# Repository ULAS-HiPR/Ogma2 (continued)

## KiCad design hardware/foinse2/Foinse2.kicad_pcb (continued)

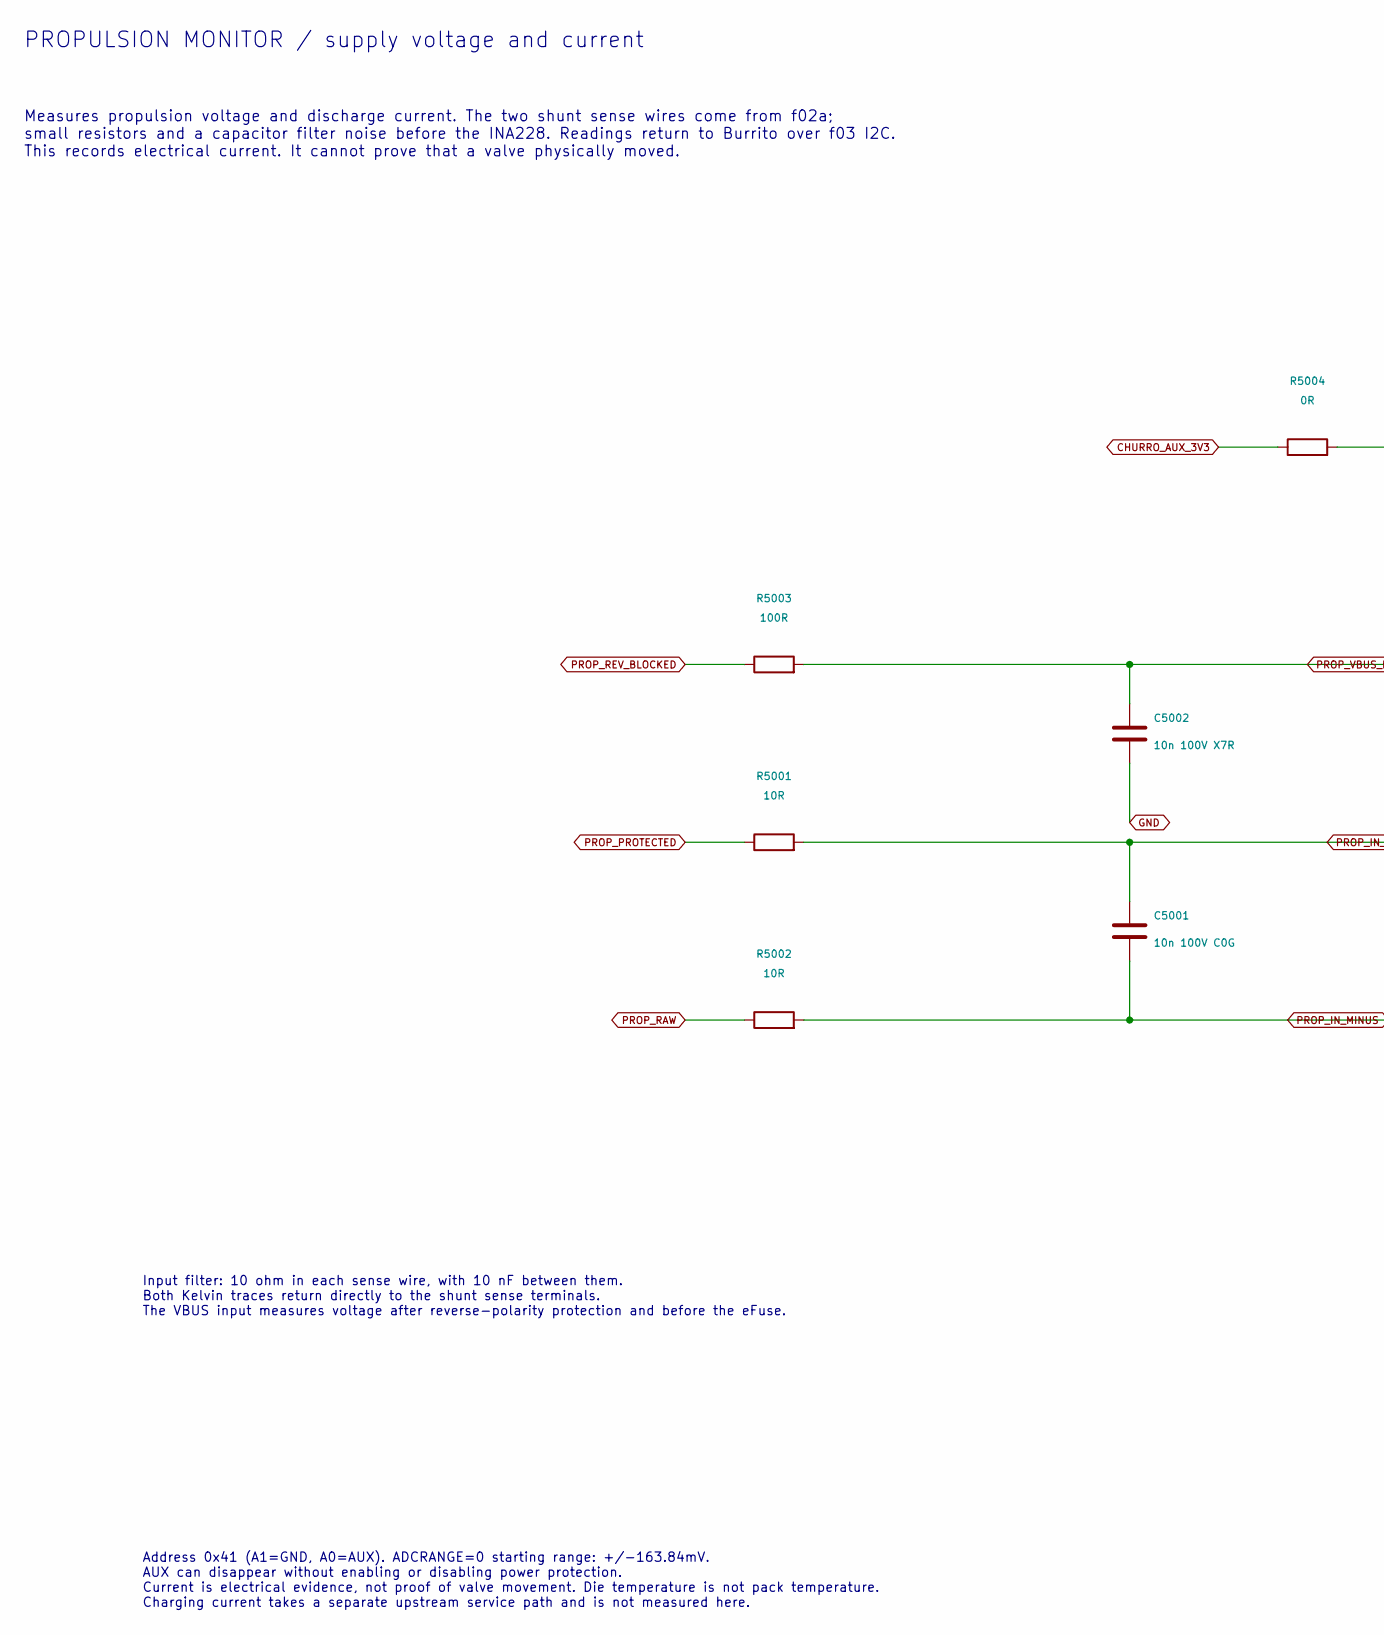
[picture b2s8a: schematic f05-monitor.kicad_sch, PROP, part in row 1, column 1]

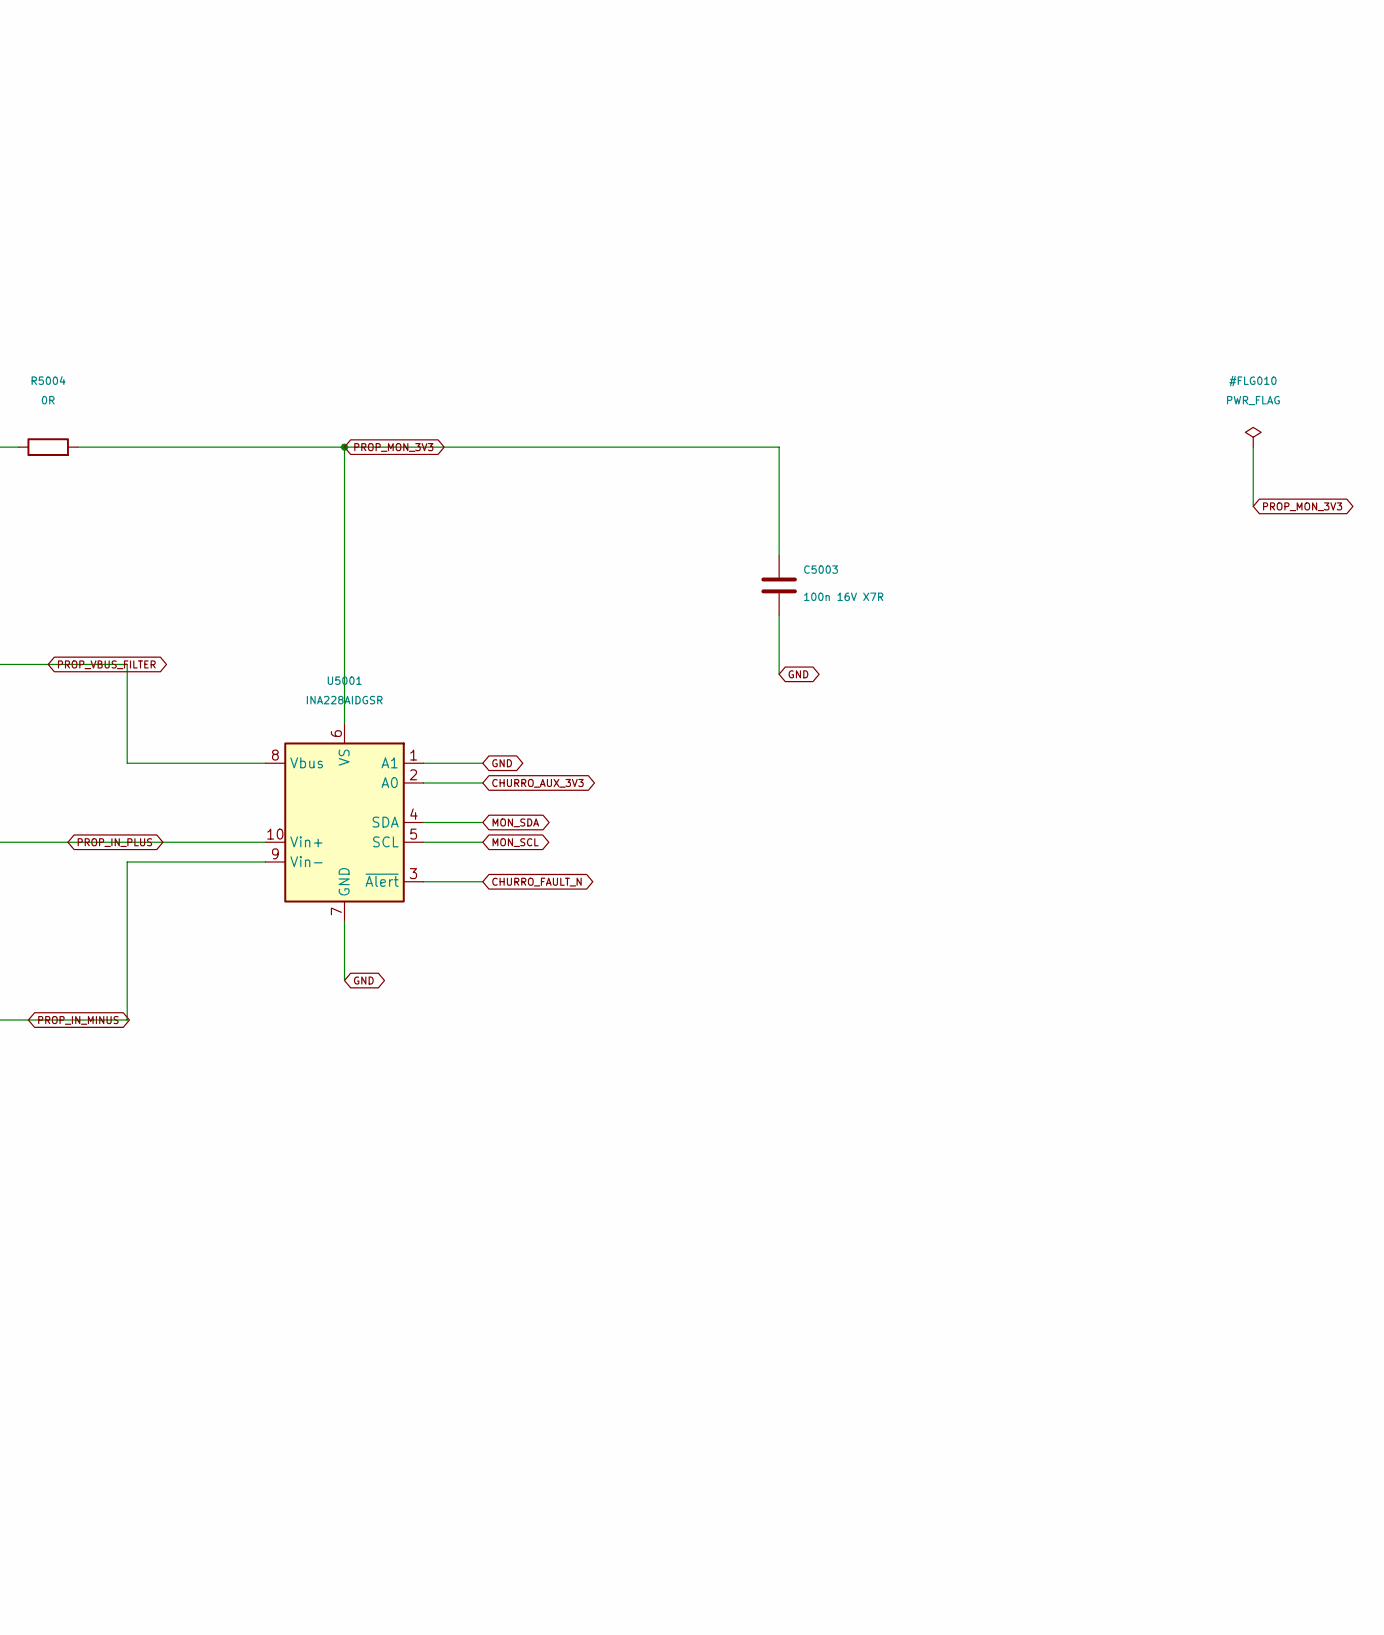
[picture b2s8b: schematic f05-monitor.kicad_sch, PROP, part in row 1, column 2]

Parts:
C5001: 10n 100V C0G; C_0603_1608Metric
C5002: 10n 100V X7R; C_0603_1608Metric
C5003: 100n 16V X7R; C_0603_1608Metric
R5001, R5002: 10R; R_0603_1608Metric
R5003: 100R; R_0603_1608Metric
R5004: 0R; R_0603_1608Metric
U5001: INA228AIDGSR; MPN INA228AIDGSR

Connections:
CHURRO_AUX_3V3: R5004.1, U5001.2 (A0); also elsewhere on the board
CHURRO_FAULT_N: U5001.3 (~Alert); also elsewhere on the board
GND: C5002.2, C5003.2, U5001.1 (A1), U5001.7 (GND); also elsewhere on the board
MON_SCL: U5001.5 (SCL); also elsewhere on the board
MON_SDA: U5001.4 (SDA); also elsewhere on the board
PROP_IN_MINUS: C5001.2, R5002.2, U5001.9 (Vin-)
PROP_IN_PLUS: C5001.1, R5001.2, U5001.10 (Vin+)
PROP_MON_3V3: C5003.1, R5004.2, U5001.6 (VS)
PROP_PROTECTED: R5001.1; also elsewhere on the board
PROP_RAW: R5002.1; also elsewhere on the board
PROP_REV_BLOCKED: R5003.1; also elsewhere on the board
PROP_VBUS_FILTER: C5002.1, R5003.2, U5001.8 (Vbus)

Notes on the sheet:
PROPULSION MONITOR / supply voltage and current
Input filter: 10 ohm in each sense wire, with 10 nF between them. Both Kelvin traces return directly to the shunt sense terminals. The VBUS input measures voltage after reverse-polarity protection and before the eFuse.
Address 0x41 (A1=GND, A0=AUX). ADCRANGE=0 starting range: +/-163.84mV. AUX can disappear without enabling or disabling power protection. Current is electrical evidence, not proof of valve movement. Die temperature is not pack temperature. Charging current takes a separate upstream service path and 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
Measures propulsion voltage and discharge current. The two shunt sense wires come from f02a; small resistors and a capacitor filter noise before the INA228. Readings return to Burrito over f03 I2C. This records electrical current. It cannot prove that a valve physically moved.

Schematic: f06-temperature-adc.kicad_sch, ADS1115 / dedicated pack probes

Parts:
C6001: 100n 16V X7R; C_0603_1608Metric
C6002, C6003: 10n 16V X7R; C_0603_1608Metric
J601: BM04B-GHS-TBT(LF)(SN); JST_GH_BM04B-GHS-TBT_1x04-1MP_P1.25mm_Vertical
R6001: 0R; R_0603_1608Metric
R6002: 10k; R_0603_1608Metric
R6003, R6004: 10k 0.1%; R_0603_1608Metric
R6005, R6006: 1k; R_0603_1608Metric
TP6001: ADC_READY; TestPoint_Pad_D1.0mm
U6001: ADS1115IDGSR; MPN ADS1115IDGSR

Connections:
ADC_3V3: C6001.1, R6001.2, R6002.1, R6003.1, R6004.1, U6001.8 (VDD); also elsewhere on the board
ADC_READY: R6002.2, TP6001.1, U6001.2 (ALERT/RDY)
AV_NTC_ADC: C6002.1, R6005.2, U6001.4 (AIN0)
AV_NTC_EXT: J601.1, R6003.2, R6005.1
AV_V_ADC: U6001.6 (AIN2); also elsewhere on the board
CHURRO_AUX_3V3: R6001.1; also elsewhere on the board
GND: C6001.2, C6002.2, C6003.2, J601.2, J601.4, U6001.1 (ADDR), U6001.3 (GND); also elsewhere on the board
MON_SCL: U6001.10 (SCL); also elsewhere on the board
MON_SDA: U6001.9 (SDA); also elsewhere on the board
PROP_NTC_ADC: C6003.1, R6006.2, U6001.5 (AIN1)
PROP_NTC_EXT: J601.3, R6004.2, R6006.1
PROP_V_ADC: U6001.7 (AIN3); also elsewhere on the board

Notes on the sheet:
PACK MONITOR / two temperature probes and two voltage readings
I2C address 0x48. Start at 128 samples/s; target 10 readings/s per channel. The programmable gain setting does not remove the ADC's physical input-voltage limits. Dedicated isolated two-wire NTC probes. No shared charger bias. Still to verify: probe resistance/temperature curve, cable protection, b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
Reads one separate temperature probe for each battery pack. Each resistor network turns the probe resistance into a voltage. Two further inputs receive the protected-rail readings from f06a. Croi supplies monitoring power and reads all four channels over the f03 I2C connection.

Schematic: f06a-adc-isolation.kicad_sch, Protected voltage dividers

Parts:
C6101, C6111: 10n 16V X7R; C_0603_1608Metric
C6103: 100n 16V X7R; C_0603_1608Metric
R6101, R6102: 22.1k 0.1%; R_0603_1608Metric
R6103, R6113: 10k 0.1%; R_0603_1608Metric
R6111, R6112: 110k 0.1%; R_0603_1608Metric
U6101: TMUX1511PWR; MPN TMUX1511PWR

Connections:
ADC_3V3: C6103.1, U6101.1 (SEL1), U6101.4 (SEL2), U6101.14 (VDD); also elsewhere on the board
AV_VMID: R6101.2, R6102.1
AV_VSCALED: C6101.1, R6102.2, R6103.1, U6101.2 (S1)
AV_V_ADC: U6101.3 (D1); also elsewhere on the board
GND: C6101.2, C6103.2, C6111.2, R6103.2, R6113.2, U6101.7 (GND), U6101.10 (SEL3), U6101.13 (SEL4); also elsewhere on the board
PROP_RAW: R6111.1; also elsewhere on the board
PROP_VMID: R6111.2, R6112.1
PROP_VSCALED: C6111.1, R6112.2, R6113.1, U6101.5 (S2)
PROP_V_ADC: U6101.6 (D2); also elsewhere on the board
VBAT_BURRITO: R6101.1; also elsewhere on the board

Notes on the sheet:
VOLTAGE MEASUREMENT / scale battery rails for the ADC
Voltage ratios: AV = 10/54.2 of its input; PROP = 10/230 of its input. At nominal 9/27 V OV boundary, one shorted top resistor gives 2.80/2.25 V. These calculations do not replace clamp, leakage, settling or partial-rail tests. Unused switch channels retain original GND straps; this is not added se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
Divides the protected 2S and 6S rail voltages down to a range the ADS1115 on f06 can measure. The analog switch separates these live dividers from the ADC when monitoring power is absent. The divider checks below are calculations only; behavior during partial power still needs testing.

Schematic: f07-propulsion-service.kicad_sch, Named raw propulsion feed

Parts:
J701: 430450200; Molex_Micro-Fit_3.0_43045-0200_2x01_P3.00mm_Horizontal

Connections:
GND: J701.2; also elsewhere on the board
PROP_RAW: J701.1; also elsewhere on the board

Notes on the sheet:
PROPULSION CONNECTION / protected battery power to the next board
J701 Micro-Fit 430450200: pin 1 PROP_RAW, pin 2 paired GND. Distinct from 4-contact propulsion input. This is not a charging connector. The provisional ~3 A aggregate limit does not allocate unspecified valve loads.
WHAT THE PROPULSION BOARD MUST HANDLE
Local regulators, valve switching, state machine, permissives and physical hazardous-energy isolation. No Churro MCU, CAN endpoint or independent-recovery supply.
SERVICE AND CHARGING / choices still depend on the packs, chargers and valve coils
Regulated 24 V actuator converter remains conditional on confirmed coil schedule. Charging uses external matched balance chargers and separately fused passive service harnesses. Charge connections join upstream of discharge protection; physical charge/arm exclusion remains required. Neither chargin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
J701 sends the 6S branch to the propulsion board after protection on f02 and the current shunt on f02a. It carries load power and its return. Valve decisions, local supplies and hazardous-energy isolation belong to propulsion, not to Churro. The service and charging boundary is recorded below.

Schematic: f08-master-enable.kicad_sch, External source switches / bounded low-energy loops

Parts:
C1006, C2006: 100n 16V X7R; C_0603_1608Metric; MPN 100n 16V X7R
D1002, D2002: BAS116,215; SOT-23; MPN BAS116,215
J103, J104: BM02B-GHS-TBT(LF)(SN); JST_GH_BM02B-GHS-TBT_1x02-1MP_P1.25mm_Vertical; MPN BM02B-GHS-TBT(LF)(SN)
R1012, R1013, R2012, R2013: 4.7k 1% 0.75W; R_2010_5025Metric; MPN CRCW20104K70FKEF
U1002, U2002: LM4040CEM3-3.0/NOPB; SOT-23; MPN LM4040CEM3-3.0/NOPB

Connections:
AV_PACK: D1002.1 (A); also elsewhere on the board
AV_SHDN_N: C1006.1, J103.2; also elsewhere on the board
AV_SWITCH_3V: J103.1, R1013.2, U1002.1 (K)
AV_SW_DIODE: D1002.3 (K), R1012.1
AV_SW_RMID: R1012.2, R1013.1
GND: C1006.2, C2006.2, U1002.2 (A), U2002.2 (A); also elsewhere on the board
PROP_PACK: D2002.1 (A); also elsewhere on the board
PROP_SHDN_N: C2006.1, J104.2; also elsewhere on the board
PROP_SWITCH_3V: J104.1, R2013.2, U2002.1 (K)
PROP_SW_DIODE: D2002.3 (K), R2012.1
PROP_SW_RMID: R2012.2, R2013.1

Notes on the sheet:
EXTERNAL ON/OFF SWITCH / two separate low-current contact loops
The external switch closes each loop to enable its battery branch: J103 controls f01; J104 controls f02. Both loops carry bounded 3 V control only. Separate switch poles; battery positives NEVER join. Unplugged/open contact -> local SHDN pull-down -> electronic OFF. No MCU or AUX dependency.
2S AV source / J103: 1 = 3 V bias, 2 = SHDN return
6S PROP source / J104: 1 = 3 V bias, 2 = SHDN return
R1006/R2006 = 22.1k local SHDN pull-downs on f01/f02. C1006/C2006 = edge filters, NOT debouncers. SHDN cycling resets a latched fault. Contact bounce can reset/retry or interrupt power; verify the installed switch. OFF still draws reference bias (~0.5 mA from 2S / ~2.3 mA from 6S, approximate). Unp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

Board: 4 copper layers, 112 parts (25 on the bottom side), 57 nets, no tracks yet.

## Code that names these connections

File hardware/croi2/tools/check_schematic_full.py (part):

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
# Reset-state rules for the MCU pins (D-22Nov.25, stage B2 brief step 7.9).
# DS14258 rev 6 (STM32H562/563 datasheet), table 14, note 7: after reset the debug pins are alternate functions, with
# internal pull-ups on PA13, PA15 and PB4 (30-50 kohm, table 58) and a pull-down on PA14, until firmware changes them.
DEBUG_PULL_UPS = frozenset({'PA13', 'PA15', 'PB4'})
# AN2606 rev 70, table 137 (STM32H562/563/573): the pins the ROM bootloader drives (USART TX, SPI MISO, I2C and I3C,
# FDCAN2 TX, USB) and the ones it only reads (USART RX, SPI SCK / MOSI / NSS, FDCAN2 RX).
BOOT_DRIVES = frozenset({'PA9', 'PA2', 'PD8', 'PA6', 'PB14', 'PC11', 'PA8', 'PC9', 'PD12', 'PD13', 'PB6', 'PB7',
                         'PB13', 'PA11', 'PA12'})
BOOT_PINS = BOOT_DRIVES | {'PA10', 'PA3', 'PD9', 'PA4', 'PA5', 'PA7', 'PB10', 'PB12', 'PC1', 'PA15', 'PC10', 'PC12', 'PB5'}
# U201's pins with an output something other than a running GPIO can drive: trace data and the debug trigger (a
# debugger), the backup domain's tamper, RTC_OUT and LSCO outputs (they outlive a system reset). ST's pin data,
# STM32H563VITx.xml (STM32_open_pin_data 45c0459, libraries/inputs/st-open-pin-data).
FLIGHT_SPECIAL_PINS = frozenset({'PE2', 'PE3', 'PE4', 'PE5', 'PE6', 'PC13', 'PC1', 'PA0', 'PA1', 'PA2', 'PB2', 'PC7', 'PC8',
                                 'PC12', 'PD2'})
FIRE_OR_ARM = re.compile(r'^(PYRO\d_(FIRE|LS_SELECT)|RECOVERY_ARM_SENSE|STAGING_ARM_SENSE|STAGE_INHIBIT_LATCHED|NEW_FLIGHT_CLEAR_REQUEST)$')


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    require(actual[('U201', '22')] != actual[('U201', '11')], 'Flight VDDA link is not bypassed by a drawing short')
    require(actual[('U401', '13')] == 'COMMS_VDDA' and actual[('U401', '19')] == 'COMMS_3V3', 'Comms VDDA/VREF+ on its own linked rail')
    for pin in ['48', '98']:
        require(actual[('U201', pin)] == 'FLIGHT_VCAP', f'Flight VCAP pad {pin} is not a 3.3 V supply')
    for pin in ['30', '62']:
        require(actual[('U401', pin)] == 'COMMS_VCAP', f'Comms VCAP pad {pin} is not a 3.3 V supply')
    require(actual[('U201', '6')] == 'FLIGHT_VBAT' and actual[('D201', '1')] == 'FLIGHT_VBAT' and actual[('D201', '2')] == 'FLIGHT_3V3',
            'Flight VBAT fed from FLIGHT_3V3 through D201, never the vehicle battery (D-6.4)')
    require(actual[('U401', '1')] == 'COMMS_3V3', 'Comms backup pin on COMMS_3V3')
    require(actual[('U401', '29')] == actual[('U4301', '1')] == 'CC_COMMS_TO_FLIGHT'
            and actual[('U401', '52')] == actual[('U4301', '8')] == 'CC_FLIGHT_TO_COMMS',
            'Inter-MCU USART3 on PB10 / PC11 through U4301 (TX from PC10, D-22Nov.25)')
    require(actual[('U4302', '4')] == 'COMMS_MR_N', 'Flight reset buffer drives comms supervisor MR, not NRST bus')
    require(actual[('U201', '14')] != actual[('U401', '7')], 'No cross-reset net short')

    # ---- GNSS and radio (unchanged by capture)
    for pin, net in {'1': 'GND', '2': 'GNSS_RX', '3': 'GNSS_TX', '4': 'GNSS_PPS', '7': 'COMMS_3V3', '8': 'COMMS_3V3',
                     '9': 'GNSS_RESET_N', '10': 'GND', '11': 'GNSS_RF', '12': 'GND'}.items():
        require(actual[('U4504', pin)] == net, f'MAX-M10S manufacturer pin {pin}: {net}')
    for pin in ['5', '6', '13', '14', '15', '16', '17', '18']:
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    require(nets['GNSS_RF'] == {('U4504', '11'), ('J4501', '1'), ('D4501', '1')}, 'Single passive GNSS RF path with ESD; no bias supply')
    require(actual[('J4501', '2')] == actual[('D4501', '2')] == 'GND', 'GNSS SMA and ESD returns')
    require(value('J4501') == '132134' and value('D4501') == 'PESD5V0F1BL,315', 'GNSS SMA and low-capacitance ESD selections (D-22Nov.8)')
    for pin, net in {'1': 'COMMS_3V3', '2': 'LORA_DIO1_MOD', '3': 'LORA_RESET_N_MOD', '4': 'LORA_MISO_MOD', '5': 'LORA_MOSI_MOD',
                     '6': 'LORA_SCK_MOD', '7': 'LORA_NCS_MOD', '8': 'LORA_BUSY_MOD', '9': 'GND', '10': 'LORA_RF_SUBG',
                     '11': 'GND', '12': 'GND', '14': 'GND', '15': 'GND', '20': 'GND'}.items():
        require(actual[('U4606', pin)] == net, f'Wio manufacturer pin {pin}: {net}')
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
    # ---- source, master enable, monitoring
    require(value('R1006') == '22.1k 1%' and actual[('R1006', '1')] == 'BAT_SHDN_N' and actual[('R1006', '2')] == 'GND', 'Source enable defaults OFF locally')
    for ref, pins in {'D1002': {'1': 'VBAT_BURRITO_INPUT', '3': 'BAT_SW_DIODE'}, 'R1012': {'1': 'BAT_SW_DIODE', '2': 'BAT_SW_RMID'},
                      'R1013': {'1': 'BAT_SW_RMID', '2': 'BAT_SWITCH_3V'}, 'U1002': {'1': 'BAT_SWITCH_3V', '2': 'GND'},
                      'J103': {'1': 'BAT_SWITCH_3V', '2': 'BAT_SHDN_N'}, 'C1006': {'1': 'BAT_SHDN_N', '2': 'GND'}}.items():
        for pin, net in pins.items():
            require(actual[(ref, pin)] == net, f'External master {ref}.{pin}: {net}')
    require(refs('BAT_SHDN_N') == {'U101', 'R1006', 'J103', 'C1006', 'D1003'}, 'Master-enable return: no firmware path except the FC_POWER_HOLD diode')
    for pin, net in {'1': 'EXT_3V3', '2': 'EXT_SCL', '3': 'EXT_SDA', '4': 'GND', '5': 'EXT_IO1', '6': 'EXT_IO2'}.items():
        require(actual[('J102', pin)] == net, f'External port J102.{pin} / {net} (D-27Nov.3)')
    require(refs('VBAT_BURRITO_INPUT') & {'J101', 'J102'} == {'J101'}, 'Battery or Churro feed through J101 only; J102 carries no battery (D-27Nov.3)')
    require(actual[('U101', '17')] == actual[('U101', '18')] == 'VBAT_SHUNT_IN', 'Both eFuse OUT pads feed upstream shunt node')
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    require(actual[('U502', '1')] != actual[('U502', '14')], 'CAN translator supply domains remain separate')
    require(actual[('U503', '3')] == actual[('U503', '5')] == actual[('U505', '3')] == actual[('U505', '5')] == 'CAN_3V3', 'Both transceivers on the switched CAN rail')
    require(refs('CAN_STB') == {'U201', 'R505', 'U502', 'U504'} and actual[('U201', '62')] == 'CAN_STB',
            'One standby line (PD15) for both buses (D-5Nov.3, D-22Nov.25)')

    # ---- status and service
    for pin, net in {'2': 'FLIGHT_STATUS_LED1', '3': 'GND', '4': 'FLIGHT_NOT_READY', '5': 'FLIGHT_3V3'}.items():
        require(actual[('U9101', pin)] == net, f'Inverter manufacturer DBV contact {pin}')
    require(value('U9101') == 'SN74LVC1G04DBVR' and actual[('R9102', '1')] == 'FLIGHT_STATUS_LED1' and value('R9102') == '47k', 'Readiness inverter and its default')
    require('BZ9001' not in dnp and actual[('D9002', '1')] == actual[('BZ9001', '1')] == 'FLIGHT_3V3'
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    require(refs(actual[('U6504', '3')]) == {'U6504', 'U6502', 'R6503'} and actual[('U6502', '1')] == 'PYRO3_FIRE'
            and actual[('U6502', '2')] == 'STAGE_ELIGIBLE', 'A7: U6504 IN only from U6502 (PYRO3_FIRE AND STAGE_ELIGIBLE)')
    require(actual[('U6001', '6')] == 'FLIGHT_NRST' and actual[('U6001', '2')] == 'STAGE_ARM_INVALID' and actual[('U6001', '1')] == 'NEW_FLIGHT_CLEAR_REQUEST'
            and actual[('U201', '88')] == 'NEW_FLIGHT_CLEAR_REQUEST' and pfunc[('U201', '88')].startswith('PD7')
            and 'R6001' in refs('NEW_FLIGHT_CLEAR_REQUEST') and value('R6001') == '100k',
            'A8: U6001 CLR = FLIGHT_NRST, D = STAGE_ARM_INVALID, CLK = PD7 with pull-down (PD15 until D-22Nov.25)')
    require(all(refs(f'OUTPUT{n}_HIGH') == {'J6601', f'U6{n + 2}04', f'R69{n}2', f'C660{2 * n - 1}'} and refs(f'PYRO{n}_ENERGY') == {f'U6{n + 2}04', f'R6{n + 2}10', f'C6{n + 2}04'}
                and actual[(f'R69{n}1', '1')] == 'FLIGHT_3V3' and refs(actual[(f'R69{n}1', '2')]) == {f'R69{n}1', f'R69{n}2'} for n in (1, 2, 3)),
            'A9: no logic rail on an armed rail; the only logic-rail path to J6601 is R69x1 / R69x2')
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        ups = [r for r in refs(net) if r.startswith('R') and ({actual[(r, '1')], actual[(r, '2')]} - {net}) & supplies]
        require(ups and all({actual[(r, '1')], actual[(r, '2')]} - {net} == {'FLIGHT_3V3'} for r in ups), f'A15: {net} pull-ups on FLIGHT_3V3')
    mag_mcu = {pfunc[k][:3] for n in ('MAG_SCL', 'MAG_SDA', 'MAG_INT') for k in nets[n] if k[0] == 'U201'}
    require(mag_mcu == {'PA8', 'PC9', 'PD3'} and refs('MAG_INT') == {'U201', 'U3701'}
            and all(refs(n) <= {'U201', 'R3702', 'R3703', 'R3704', 'R3705'} for n in ('MAG_SCL', 'MAG_SDA')),
            'A16: magnetometer nets land on PA8, PC9 and PD3 only (INT on PE6 until D-22Nov.25)')
    require(refs('USB_VBUS') == {'J4401', 'D4401', 'C4401', 'C4402', 'U4401', 'R1208'}, 'A18: USB VBUS only to its ESD, decoupling, U4401 and the R1208 divider')
    for ref in ('R1701', 'R1801'):
        bottom = next(r for r in refs(actual[(ref, '2')]) if r.startswith('R') and r != ref)
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            'A26: fire, low-side, new-flight, arm-sense and latch pins carry no trace, debug-trigger, tamper, RTC_OUT or LSCO '
            'output (D-22Nov.25)')
    a24, a25 = reset_pin_faults(root)
    require(not a24, 'A24: no pulled-down net (an output off by default) on a debug pin pulled up from reset (PA13, PA15, PB4) '
                     'or a pin the ROM bootloader drives (D-22Nov.25)')
    require(not a25, 'A25: no fire, low-side, arm-sense or staging-latch net on a pin the ROM bootloader drives or reads (D-22Nov.25)')

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
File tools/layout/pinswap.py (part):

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- clocks, debug, USB, power, BOOT0 and NRST stay.

Where a net may go (a move only; a net may stay where it was captured):
- never: SWD (PA13, PA14), PB3 (JTDO), PC13 (kept quiet beside the LSE, the pin map's erratum note), PC14, PC15, PH0, PH1,
  and any pin the pin map reserves (comms PC3 and PC4, for the radio's RX and TX enables);
- the pins the ROM bootloader drives once it has found its host (AN2606 rev. 70, table 137, STM32H562/563/573: the
  USART TX pins PA9, PA2, PD8; SPI MISO PA6, PB14, PC11; I2C3 PA8, PC9; I2C4 PD12, PD13; I3C PB6, PB7; FDCAN2 TX PB13;
  USB PA11, PA12): only a spare test pad, which has nothing on it but a pad (and a spare pad moves nowhere else);
- PA15 and PB4, which are pulled up from reset (as JTDI and NJTRST; DS14258 rev 6, table 14, note 7) until firmware
  changes them, and the pins the bootloader only reads (RX PA10, PA3, PD9; SPI SCK, MOSI and NSS PA5, PA7, PA4, PB10,
  PC1, PB12, PC10, PC12, PA15; FDCAN2 RX PB5): any net but an output that must stay off by default, an arm sense or
  the staging inhibit (the checker's rule: no fire or arm net on a bootloader pin);
- every other I/O pin: any net its function allows.
The outputs that must stay off by default (the enables with pull-downs, every fire and low-side select, the strobe)
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PIN_XML = {'U201': INPUTS / 'st-open-pin-data' / 'STM32H563VITx.xml', 'U401': INPUTS / 'st-open-pin-data' / 'STM32H563RITx.xml'}
PIN_CSV = {'U201': INPUTS / 'flight-pinout.csv', 'U401': INPUTS / 'comms-pinout.csv'}

NEVER = {'PA13', 'PA14', 'PB3', 'PC13', 'PC14', 'PC15', 'PH0', 'PH1'}
BOOT_DRIVES = {'PA9', 'PA2', 'PD8', 'PA6', 'PB14', 'PC11', 'PA8', 'PC9', 'PD12', 'PD13', 'PB6', 'PB7', 'PB13', 'PA11', 'PA12'}
PULLED_OR_READ = {'PA15', 'PB4', 'PA10', 'PA3', 'PD9', 'PA5', 'PA7', 'PA4', 'PB10', 'PC1', 'PB12', 'PC10', 'PC12', 'PB5'}
NO_DEST = NEVER | BOOT_DRIVES | PULLED_OR_READ           # where an off-by-default output pays the penalty
HARMLESS = re.compile(r'^TP_P[A-K]\d+$')                # spare test pads, named for their pin: a pad and nothing else
ARM = {'RECOVERY_ARM_SENSE', 'STAGING_ARM_SENSE', 'STAGE_INHIBIT_LATCHED'}   # never on a bootloader or pulled pin
MIN_GAIN = 1.0
MUST_AVOID = {'FC_POWER_HOLD', 'SERVICE_POWER_EN', 'CAN_POWER_EN', 'NOR_EN', 'FLIGHT_COMMS_EN', 'CHURRO_RETURN_EN',
              'TP_STROBE', 'NEW_FLIGHT_CLEAR_REQUEST', 'GNSS_EN', 'LORA_EN',
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                self.notes[net] = row['notes']
                if 'EXTI' in row['notes']:
                    self.exti.add(net)
        # pins the map reserves (comms PC3 / PC4 for the radio's RX and TX enables): never a destination
        self.reserved = {row['pad'] for row in csv.DictReader(open(PIN_CSV[ref])) if 'Reserved' in row['notes']}
        self.start = dict(self.net_at)

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
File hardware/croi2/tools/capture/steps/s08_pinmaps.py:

"""Step 8b, close-out: the as-captured pin maps.

libraries/inputs/{flight,comms}-pinout.csv become the as-captured allocations with exact native net
names. The 7 September versions (functional shorthand) move to history/baseline-2026-09-08/inputs.

Flight: the 22 September 100-pad map (docs/architecture/proposed-flight-pinout.csv) amended by the
capture specification's "Flight pad changes" row: 23 pads.
Comms: the 64-pad map (docs/architecture/proposed-comms-pinout.csv), with PC3 / PC4 unconnected
as drawn at step 7 (the map's "MCU-only reservation, no external connection").

Every alternate-function row of both maps is checked against ST's open pin data (as in step 7).
"""
import csv
import io
import re
import shutil
import sys
import xml.etree.ElementTree as ET
from pathlib import Path

BOARD = Path(__file__).resolve().parents[3]
REPO = BOARD.parents[1]
DOCS = REPO / 'docs/architecture'
INPUTS = BOARD / 'libraries/inputs'
ARCHIVE = BOARD / 'history/baseline-2026-09-08/inputs'
PINDATA = Path('/tmp/claude-0/pindata/mcu')
FIELDS = ['role', 'mpn', 'pad', 'port_or_supply', 'net', 'function', 'alternate_function', 'notes']

FLIGHT = {  # pad: (net, function, AF, note) from the capture specification's flight pad changes
    '4': ('FC_POWER_HOLD', 'GPIO', '', 'Output; R1015 1M pull-down; high after launch detect (D-2Nov.18)'),
    '5': ('MAG_INT', 'GPIO', '', 'EXTI6; optional magnetometer data-ready (D-2Nov.11)'),
    '6': ('FLIGHT_VBAT', 'BACKUP_SUPPLY', '', 'D201 from FLIGHT_3V3; C207 100nF and C219 100uF (D-6.4)'),
    '26': ('RESET_MEMORY', 'GPIO', '', 'Input; reset-memory RC node (D-19Nov.3)'),
    '35': ('TP_STROBE', 'GPIO', '', 'Output; R203 to TP201 timing strobe; R205 holds it low at reset (D-19Nov.3)'),
    '38': ('PYRO1_FIRE', 'GPIO', '', 'Output; U6304 IN; R6303 100k pull-down (D-6.2, D-2Nov.1)'),
    '39': ('SERVICE_POWER_EN', 'GPIO', '', 'Output; U1601 EN; R1602 pull-down (D-6.5)'),
    '40': ('PYRO2_FIRE', 'GPIO', '', 'Output; U6404 IN; R6403 100k pull-down (D-6.2, D-2Nov.1)'),
    '41': ('CAN_STB', 'GPIO', '', 'Output; standby for both transceivers (D-5Nov.3)'),
    '43': ('PYRO3_FIRE', 'GPIO', '', 'Output; U6502 AND with STAGE_ELIGIBLE; R6501 100k pull-down (D-7.2)'),
    '44': ('RECOVERY_ARM_SENSE', 'GPIO', '', 'Input; U6103 OUTA via R6107 (D-5Nov.3)'),
    '45': ('STAGE_INHIBIT_LATCHED', 'GPIO', '', 'Input; U6001 Q-bar via R6005 1k (D-7.2)'),
    '46': ('STAGING_ARM_SENSE', 'GPIO', '', 'Input; STAGE_ARM_INVALID via R6108, read inverted (D-7.2, D-2Nov.11)'),
    '57': ('TP_PD10', 'GPIO', '', 'Spare test pad TP204; input with pull-down (D-19Nov.3)'),
    '61': ('PYRO3_LS_SELECT', 'GPIO', '', 'Output; Q6501 gate via R6504; R6502 100k pull-down (D-5Nov.3)'),
    '63': ('TP_PC6', 'GPIO', '', 'Spare test pad TP202; input with pull-down (D-19Nov.3)'),
    '64': ('TP_PC7', 'GPIO', '', 'Spare test pad TP203; input with pull-down; never drives, neighbours PC8 (D-19Nov.3)'),
    '65': ('PYRO2_LS_SELECT', 'GPIO', '', 'Output; Q6401 gate via R6404; R6402 100k pull-down (D-5Nov.3)'),
    '66': ('MAG_SDA', 'I2C3_SDA', 'AF4', 'Via R3705 22R; R3703 2.7k pull-up (D-2Nov.11)'),
    '67': ('MAG_SCL', 'I2C3_SCL', 'AF4', 'Via R3704 22R; R3702 2.7k pull-up (D-2Nov.11)'),
    '68': ('PYRO1_LS_SELECT', 'GPIO', '', 'Output; Q6301 gate via R6304; R6302 100k pull-down (D-2Nov.1)'),
    '69': ('CAN2_TX', 'FDCAN2_TX', 'AF9', 'Bus 2 via U504 (D-5Nov.3)'),
    '91': ('CAN2_RX', 'FDCAN2_RX', 'AF9', 'Bus 2 via U504 (D-5Nov.3)'),
}
COMMS = {'11': 'Reserved LORA_RXEN: MCU-only, no external connection (no-connect); safe low or analog',
         '24': 'Reserved LORA_TXEN: MCU-only, no external connection (no-connect); safe low or analog'}
DEBUG = {'SWD': ('DEBUG_JTMS-SWDIO', 'DEBUG_JTCK-SWCLK'), 'TRACESWO': ('DEBUG_JTDO-SWO',)}


def af_check(rows, xml):
    ns = {'m': 'http://dummy.com'}
    pins = {p.get('Position'): (p.get('Name'), [s.get('Name') for s in p.findall('m:Signal', ns)])
            for p in ET.parse(PINDATA / xml).getroot().findall('m:Pin', ns)}
    af = {}
    for gp in ET.parse(PINDATA / 'IP/GPIO-STM32H56x_gpio_v1_0_Modes.xml').getroot().iter():
        port = re.match(r'P[A-Z]\d+', gp.get('Name', '')) if gp.tag.endswith('GPIO_Pin') else None
        for ps in (gp if port else []):
            if ps.tag.endswith('PinSignal'):
                af[(port.group(0), ps.get('Name'))] = [v.text for v in ps.iter() if v.tag.endswith('PossibleValue')]
    n = 0
    for r in rows:
        name, signals = pins[r['pad']]
        want = r['port_or_supply'].split('/')[0]
        assert re.match(rf'{re.escape(want)}(\W|$)', name), (r['pad'], want, name)
        if r['alternate_function'] == 'ANALOG':                       # ADC inputs: the channel is on the pad
            assert r['function'] in signals, (r['pad'], r['function'], signals)
            n += 1
        elif r['alternate_function']:
            sig = [s for s in DEBUG.get(r['function'], (r['function'],)) if s in signals]
            assert len(sig) == 1, (r['pad'], r['function'])
            assert any(v.startswith(f"GPIO_{r['alternate_function']}_") for v in af[(want, sig[0])]), (r['pad'], sig)
            n += 1
    return n


def write(path, rows):
    buf = io.StringIO()
    w = csv.DictWriter(buf, FIELDS, quoting=csv.QUOTE_ALL, lineterminator='\n')
    w.writeheader()
    w.writerows(rows)
    path.write_text(buf.getvalue())


def build():
    flight = list(csv.DictReader((DOCS / 'proposed-flight-pinout.csv').open()))
    for r in flight:
        if r['pad'] in FLIGHT:
            r['net'], r['function'], r['alternate_function'], r['notes'] = FLIGHT[r['pad']]
    comms = list(csv.DictReader((DOCS / 'proposed-comms-pinout.csv').open()))
    for r in comms:
        if r['pad'] in COMMS:
            r['net'], r['function'], r['notes'] = 'NC', 'ANALOG', COMMS[r['pad']]
    assert len(flight) == 100 and len(comms) == 64
    counts = af_check(flight, 'STM32H563VITx.xml'), af_check(comms, 'STM32H563RITx.xml')
    ARCHIVE.mkdir(parents=True, exist_ok=True)
    for name, rows in (('flight-pinout.csv', flight), ('comms-pinout.csv', comms)):
        if not (ARCHIVE / name).exists():
            shutil.copy2(INPUTS / name, ARCHIVE / name)
        write(INPUTS / name, rows)
    return counts


if __name__ == '__main__':
    print('alternate-function rows checked against ST data (flight, comms):', build())

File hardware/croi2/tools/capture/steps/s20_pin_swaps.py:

"""Step 20: U201's fire-logic pins, re-dealt so the fire logic's runs don't cross (take 2, D-23Nov.25).

Seán, 23 Nov: "swap U201's pins so the fire pins face the output stage, run ST's pin check"; standing rule D-23Nov.16:
"Do not feel like you can't change pin functions. If you check and it can work, do it."

The output stage is north of U201, beyond its top row (pads 76-100). The fire pins can't face it: A26 keeps them on port
E, and the top row's one port-E pin, PE0 (pad 97), sits beside VCAP (pad 98), a supply pad, which D-22Nov.25's
neighbour rule bars for a fire pin (pad 98 is VCAP, not PE1, on this package; PE2-PE6 on the west side carry trace
outputs). So the fire pins stay on the bottom row's three legal pins, and what can face north does: channel 3's low side
takes PD4, port D being the one other port with a legal top-row pin. Then, west to east, no run crosses another on L3:

- the two low sides at the board's top left leave from the bottom row's west end (PC4, PB1);
- PYRO1_FIRE from PE7, up the lane under U201 that the budget kept, then north-west to U6304 and R6303;
- PYRO3_LS_SELECT north from PD4, between channel 1's high side and channel 2's, to R6504 and R6502;
- PYRO2_FIRE from PE9, under U201 to its east side and north to U6404 and R6403;
- PYRO3_FIRE from PE15, under U201 to its north-east corner and on to U6502.

The moves, a swap and a cycle:
- PYRO2_FIRE PE15 (46) -> PE9 (40); PYRO3_FIRE PE9 -> PE15. The fire pins' neighbours don't change.
- PYRO3_LS_SELECT PC6 (63) -> PD4 (85); PYRO1_LS_SELECT PD4 -> PC4 (33); ADC_FLIGHT_3V3 PC4 -> PB0 (35), ADC1 input 4
  to input 9; FLIGHT_COMMS_EN PB0 -> PC6, its load (U1202, R1205) being south of U201 either way.

Checked by the checker (A24, A25: no pulled-down output on a debug pull-up or bootloader pin, no fire, low-side,
arm-sense or latch net on a bootloader pin; A26, now with D-22Nov.25's whole neighbour rule) and by step 20's check.
Every fire pin is a plain GPIO that wakes as an analog input (no pull) with its 100 kohm pull-down outside, so it stays
low through reset and boot: none is a debug pin (pulls at reset) or a pin the ROM bootloader drives or reads (AN2606).

Edits the flight MCU's sheet in place (the six pins trade labels) and the flight pin map.
"""
import csv
import io
import re
import sys
from pathlib import Path
sys.path.insert(0, str(Path(__file__).resolve().parents[1]))
sys.path.insert(0, str(Path(__file__).resolve().parent))
import kicadsch as K
from s19_pin_swaps import st_data

BOARD = Path(__file__).resolve().parents[3]
SHEET = '02-flight-mcu.kicad_sch'
MAP = BOARD / 'libraries' / 'inputs' / 'flight-pinout.csv'
FIELDS = ['role', 'mpn', 'pad', 'port_or_supply', 'net', 'function', 'alternate_function', 'notes']
D = 'D-23Nov.25'

# (net, from pad, to pad) on U201
MOVES = [('PYRO2_FIRE', '46', '40'), ('PYRO3_FIRE', '40', '46'),
         ('PYRO3_LS_SELECT', '63', '85'), ('PYRO1_LS_SELECT', '85', '33'), ('ADC_FLIGHT_3V3', '33', '35'),
         ('FLIGHT_COMMS_EN', '35', '63')]
WHY = {
    'PYRO2_FIRE': 'from PE9 its run passes under U201 west of channel 3\'s, to the east side',
    'PYRO3_FIRE': 'PE15 is the fire pin nearest U6502, the east-most target',
    'PYRO3_LS_SELECT': 'PD4 faces the output stage, between channel 1 and channel 2',
    'PYRO1_LS_SELECT': 'from PC4 it joins channel 2\'s low side west of the fire pins',
    'ADC_FLIGHT_3V3': 'a low side takes PC4; PB0 is on the same converter',
    'FLIGHT_COMMS_EN': 'a low side takes PD4',
}


def relabel():
    t = K.load(BOARD / SHEET)
    pins = K.pin_positions(t, 'U201')
    found = {}
    for _, a, b in MOVES:
        for pad in (a, b):
            pts, used = K.connected_points(t, pins[pad][:2])
            labs = K.labels_at(t, pts)
            assert len(labs) == 1, ('U201', pad, [l[1] for l in labs])
            found[pad] = labs[0]
    olds = {pad: lab[1] for pad, lab in found.items()}
    for net, a, b in MOVES:
        assert olds[a] == net, (net, a, olds[a])
        found[b][1] = net
    K.save(t, BOARD / SHEET)


def remap():
    sig, _ = st_data('U201')
    rows = list(csv.DictReader(open(MAP)))
    by_pad = {r['pad']: r for r in rows}
    old = {r['net']: dict(r) for r in rows}
    for net, a, b in MOVES:
        o, r = old[net], by_pad[b]
        assert o['pad'] == a, (net, o)
        f = o['function']
        m = re.match(r'(ADC\d)_INP\d+$', f)
        if m:                                  # the new pin's channel on the same converter
            ch = [s for s in sig[b] if re.match(rf'{m.group(1)}_INP\d+$', s)]
            assert len(ch) == 1, (net, b, ch)
            f = ch[0]
        else:
            assert f == 'GPIO' and 'GPIO' in sig[b], (net, b, f)
        note = f"{o['notes']}; from {o['port_or_supply']} (pad {a}): {WHY[net]} ({D})"
        r.update(net=net, function=f, alternate_function=o['alternate_function'], notes=note)
    buf = io.StringIO()
    w = csv.DictWriter(buf, fieldnames=FIELDS, quoting=csv.QUOTE_ALL, lineterminator='\n')
    w.writeheader()
    w.writerows(rows)
    MAP.write_text(buf.getvalue())


if __name__ == '__main__':
    relabel()
    remap()
    print('step 20:', len(MOVES), 'nets moved on U201:', ', '.join(f'{n} {a}->{b}' for n, a, b in MOVES))

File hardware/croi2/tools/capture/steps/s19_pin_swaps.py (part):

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signal to another pin with the same signal. This step takes each new ADC channel and AF number from the same data.

The rules the search kept, and why:
- The fault the brief asked to verify first holds. After reset PA15 is JTDI with an internal pull-up, as are PA13 and
  PB4 (DS14258 rev 6, table 14, note 7), of 30-50 kohm (table 58). Against R7002's 100 kohm that holds
  CHURRO_RETURN_EN at 2.2-2.5 V from reset until firmware drives PA15: over the TPS2553's 1.1 V enable threshold
  (SLVS841G) and the TMUX1511's 1.2 V select threshold (SCDS390B), so U7001 powered Churro's aux rail and U7002
  joined its I2C and fault lines at every power-up. It moves off PA15.
- The ROM bootloader drives some pins (AN2606 rev 70, table 137): USART1 TX on PA9 held PYRO1_LS_SELECT, USB on PA11
  and PA12 held NOR_EN and FLIGHT_COMMS_EN. They move; the three spare test pads take those pins, a pad and nothing
  else, and are renamed for them.
- No pulled-down output sits on a pulled-up debug pin or a pin the bootloader drives; no fire, low-side, arm-sense or
  staging-latch net sits on any bootloader pin; the fire pins stay on port E and the low-side selects on three other
  ports; no fire pin or low-side select is beside another, an arm sense, the staging latch or the new-flight request
  (as captured, PE12 sat beside PE13 and PD14 beside PD15); and none of them is on a pin with a trace, debug-trigger,
  tamper, RTC_OUT or LSCO output. The checker holds each (A24-A26).

Edits the MCU sheets in place: U201's moves trade labels; on U401's sheet six nets move onto pins that had no-connect
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}
# why a net left its pin, where the reason is not distance
LEFT = {
    'CHURRO_RETURN_EN': "PA15's reset pull-up held U7001 and U7002 on until firmware ran",
    'PYRO1_LS_SELECT': 'the ROM bootloader drives PA9 as USART1 TX',
    'NOR_EN': 'the ROM bootloader drives PA11 as USB D-',
    'FLIGHT_COMMS_EN': 'the ROM bootloader drives PA12 as USB D+',
    'PYRO2_LS_SELECT': 'PC8 carries trace data (TRACED1)',
    'PYRO3_FIRE': 'PE12 sits beside the recovery arm sense on PE13',
    'PYRO3_LS_SELECT': 'PD14 sits beside the new-flight request on PD15',
}
# what a pin brings to whatever it carries; and the old notes that belonged to the pin, not the net
PIN_FACT = {
    ('U201', 'PA9'): 'the ROM bootloader drives it as USART1 TX: a pad and nothing else here',
    ('U201', 'PA11'): 'VDDUSB powered; the ROM bootloader drives it as USB D-: a pad and nothing else here',
    ('U201', 'PA12'): 'VDDUSB powered; the ROM bootloader drives it as USB D+: a pad and nothing else here',
    ('U201', 'PA15'): 'JTDI with an internal pull-up from reset (DS14258 table 14 note 7) until firmware sets it',
    ('U201', 'PB4'): 'NJTRST with an internal pull-up from reset (DS14258 table 14 note 7) until firmware sets it',
}
PIN_ONLY = ('; VDDUSB powered', '; disable JTAG beyond SWD', '; never drives, neighbours PC8')
STALE_TP = {'TP201': 'TP19'}                    # the strobe's loop since the test points were renumbered


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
